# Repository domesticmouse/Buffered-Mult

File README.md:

# Buffered-Mult

A 3-channel active buffered mult (multiple) circuit designed for Eurorack modular synthesizers. View this in [KiCanvas](https://kicanvas.org/?repo=https%3A%2F%2Fgithub.com%2Fdomesticmouse%2FBuffered-Mult).

See [domesticmouse/BufferedMult-SKiDL](https://github.com/domesticmouse/BufferedMult-SKiDL) for an improved (and simplified) re-implementation.

## Purpose

In modular synthesis, a **multiple** is used to split a single signal (such as control voltage, gates/triggers, or audio) and route it to multiple destinations simultaneously.

While passive multiples simply wire jacks together in parallel, they cause **voltage droop** when splitting precise voltages like 1V/Octave pitch CV across multiple inputs due to impedance loading. This results in out-of-tune oscillators and pitch tracking errors.

This **buffered mult circuit** solves that problem by using active operational amplifiers configured as unity-gain buffers:

- **1:1 Voltage Precision:** Maintains accurate voltage levels (essential for 1V/Oct pitch CV) across all outputs without signal drop.
- **Impedance Isolation:** High input impedance presents virtually no load to the source signal, while low output impedance cleanly drives downstream module inputs.
- **Channel Isolation:** Prevents attached modules from loading or interfering with each other.

---

## Specifications

### Dimensions
- **Height:** 3U (Eurorack format)
- **Width:** 6HP
- **Faceplate:** Complete mechanical specifications and KiCad panel design are available in [`faceplate/README.md`](faceplate/README.md).

See Exploding Shed's [Eurorack Dimensions Guide](https://www.exploding-shed.com/synth-diy-guides/standards-of-eurorack/eurorack-dimensions/) for sizing a 6hp module.

### Inputs
- **3× 3.5 mm mono input jacks:**
  - Input 2 is normalled to Input 1.
  - Input 3 is normalled to Input 2.
- **Cascading Normalling Routing:**
  - **1 Input patched (Input 1):** Functions as a **1×9** mult (1 input split to 9 outputs).
  - **2 Inputs patched (Inputs 1 & 2):** Functions as **1×3** (Input 1) and **1×6** (Input 2) mults.
  - **3 Inputs patched (Inputs 1, 2 & 3):** Functions as **3 independent 1×3** mults.
- **100 kΩ pulldown resistors** (`R1`–`R3`) on inputs to prevent floating inputs when unpatched.
- **Input ESD & RF Filtering:** 1 kΩ series resistors (`R16`–`R18`) and 100 pF capacitors (`C9`–`C11`) provide high-frequency noise filtering and ESD protection.

### Outputs
- **9× 3.5 mm mono output jacks:** 3 dedicated buffered outputs for each of the 3 input channels.
- **1 kΩ Short-Circuit Protection:** Output series resistors (`R7`–`R15`) protect op-amps during cable insertion/patching shorts while maintaining stability under capacitive cable loads.
- **Bipolar LED Indication:** Opposing-polarity LED pairs (`D1`–`D6`) driven by dedicated active op-amp constant-current stages (`R4`–`R6`) indicate positive (+) and negative (-) voltage states without loading signal lines.

---

## Circuit & Physical Design

- **TL074 Quad Operational Amplifiers:** Configured as high-impedance unity-gain buffers (`U1`, `U2`, `U3`).
- **Active Visual Feedback:** 4th op-amp stage on each TL074 drives bipolar indicator LEDs in a constant-current feedback arrangement.
- **Power Connector:** Standard 2×5-pin IDC header (`J1`) for Eurorack ±12V power connection.
- **Power Filtering & Decoupling:** Bulk 10 µF electrolytic capacitors (`C7`, `C8`) on power entry rails plus 100 nF ceramic decoupling capacitors (`C1`–`C6`) per IC package.
- **Reverse Power Protection:** MBR0520 Schottky diodes (`D7`, `D8`) protect against reverse ribbon cable insertion.
- **Two-Sided Board Layout:** All SMT components on top layer (`F.Cu`); through-hole jacks and LEDs on bottom layer (`B.Cu`) for front panel mounting.

---

## Verification & Fabrication

- **KiCad Electrical Rules Check (ERC):** 0 Errors, 0 Warnings on main board schematic.
- **KiCad Design Rules Check (DRC):** 0 Track / Clearance Errors on main board and faceplate PCB.
- **JLCPCB Automated Assembly Ready:** Complete Gerber ZIP, SMT BOM (`BOM-Buffered-Mult.csv`), and Centroid CPL (`CPL-Buffered-Mult.csv`) generated in [`jlcpcb/production_files/`](jlcpcb/production_files/).
- **Faceplate Fabrication:** Complete KiCad project, panel Gerber files, and drill specs in [`faceplate/`](faceplate/).

## License

BufferedMult is open source and available under the [Apache License 2.0](LICENSE).

## Disclaimer

This is not an official Google product.

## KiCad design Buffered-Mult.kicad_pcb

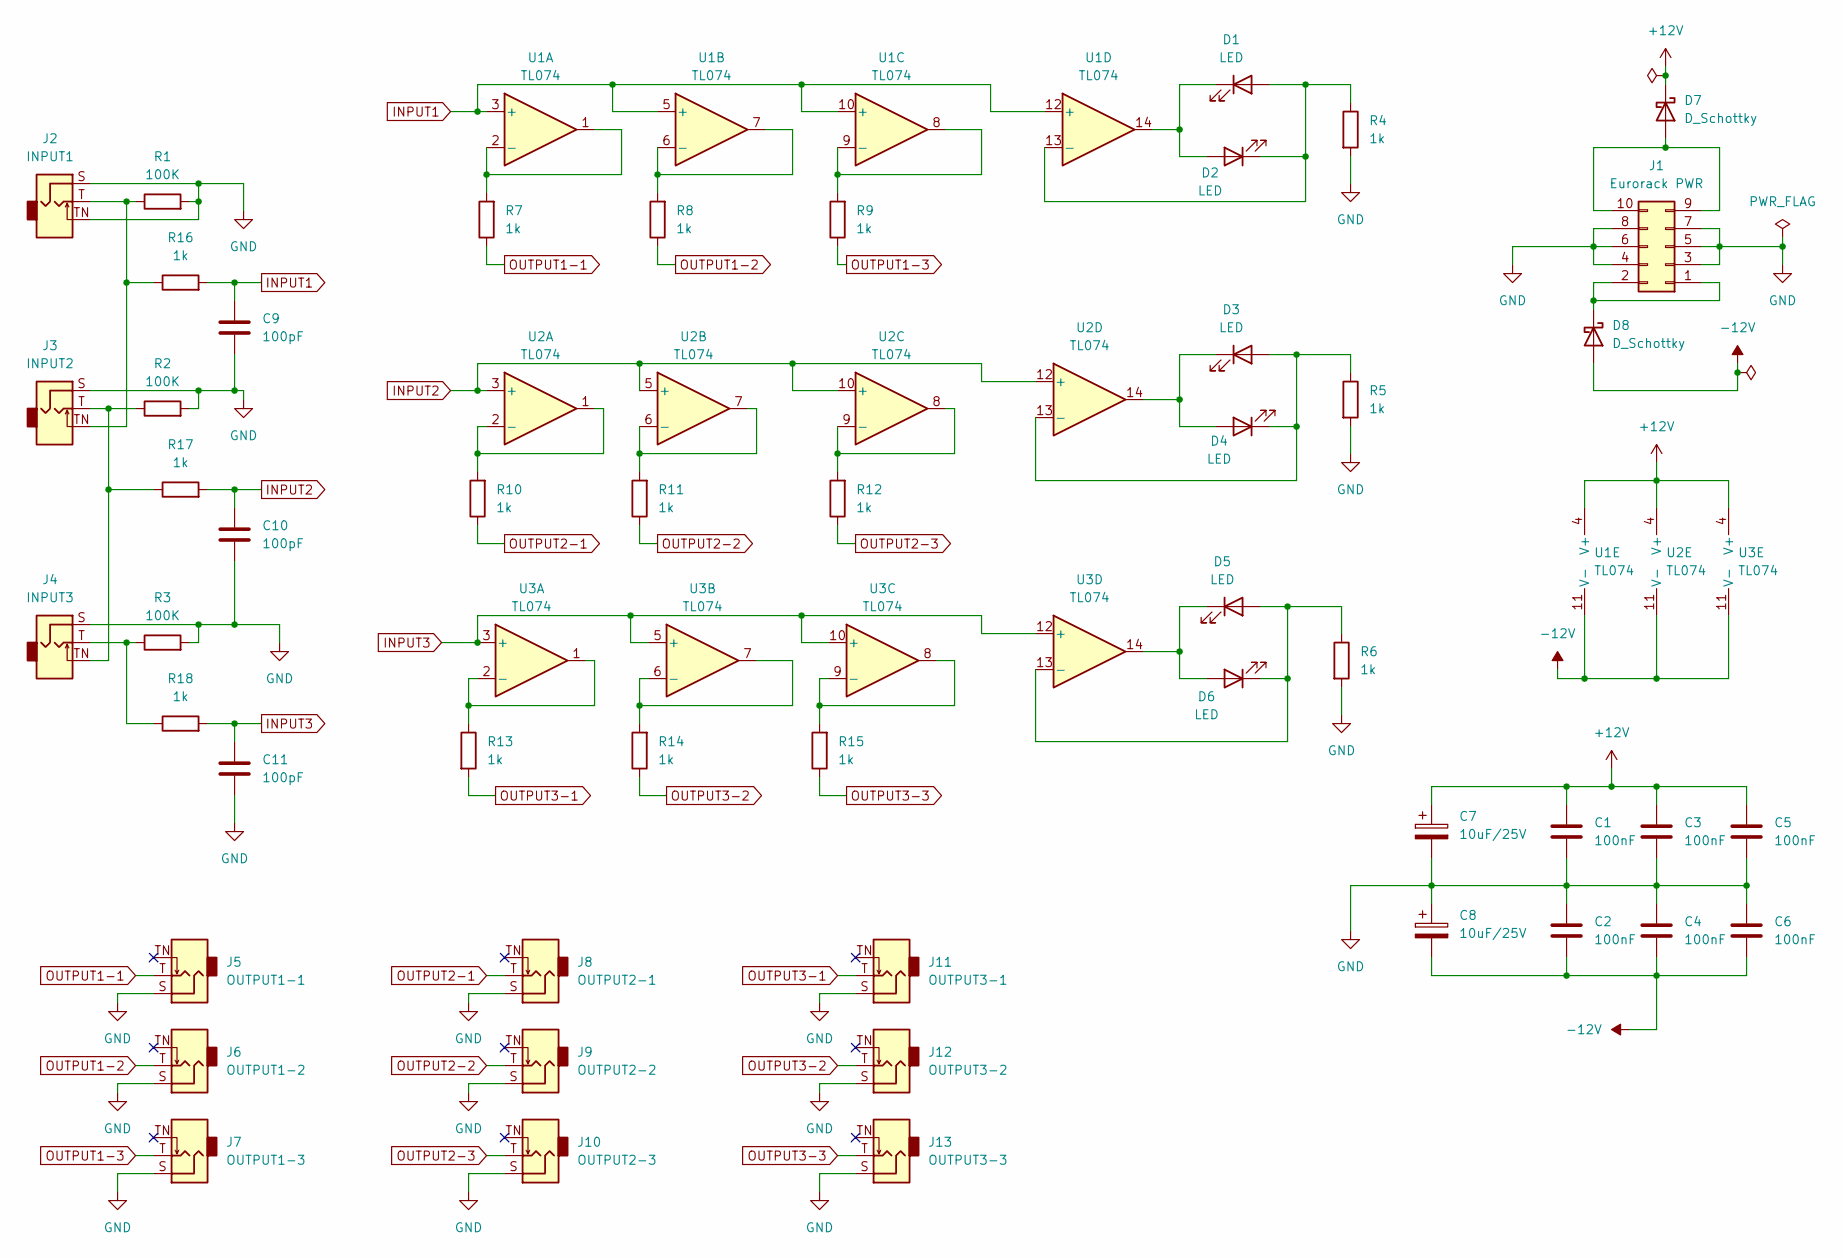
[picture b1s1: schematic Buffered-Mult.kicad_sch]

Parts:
C1, C2, C3, C4, C5, C6: 100nF; C_0603_1608Metric_Pad1.08x0.95mm_HandSolder; LCSC C14663
C7, C8: 10uF/25V; CP_Elec_5x5.4; LCSC C46550416
C9, C10, C11: 100pF; C_0603_1608Metric_Pad1.08x0.95mm_HandSolder; LCSC C14858
D1, D2, D3, D4, D5, D6: LED; LED_D3.0mm_FlatTop
D7, D8: D_Schottky; D_SMA_Handsoldering; LCSC C2480
J1: Eurorack PWR; IDC-Header_2x05_P2.54mm_Vertical
J2: INPUT1; Jack_3.5mm_QingPu_WQP-PJ398SM_Vertical_CircularHoles
J3: INPUT2; Jack_3.5mm_QingPu_WQP-PJ398SM_Vertical_CircularHoles
J4: INPUT3; Jack_3.5mm_QingPu_WQP-PJ398SM_Vertical_CircularHoles
J5: OUTPUT1-1; Jack_3.5mm_QingPu_WQP-PJ398SM_Vertical_CircularHoles
J6: OUTPUT1-2; Jack_3.5mm_QingPu_WQP-PJ398SM_Vertical_CircularHoles
J7: OUTPUT1-3; Jack_3.5mm_QingPu_WQP-PJ398SM_Vertical_CircularHoles
J8: OUTPUT2-1; Jack_3.5mm_QingPu_WQP-PJ398SM_Vertical_CircularHoles
J9: OUTPUT2-2; Jack_3.5mm_QingPu_WQP-PJ398SM_Vertical_CircularHoles
J10: OUTPUT2-3; Jack_3.5mm_QingPu_WQP-PJ398SM_Vertical_CircularHoles
J11: OUTPUT3-1; Jack_3.5mm_QingPu_WQP-PJ398SM_Vertical_CircularHoles
J12: OUTPUT3-2; Jack_3.5mm_QingPu_WQP-PJ398SM_Vertical_CircularHoles
J13: OUTPUT3-3; Jack_3.5mm_QingPu_WQP-PJ398SM_Vertical_CircularHoles
R1, R2, R3: 100K; R_0603_1608Metric_Pad0.98x0.95mm_HandSolder; LCSC C25803
R4, R5, R6, R7, R8, R9, R10, R11, R12, R13, R14, R15, R16, R17, R18: 1k; R_0603_1608Metric_Pad0.98x0.95mm_HandSolder; LCSC C21190
U1, U2, U3: TL074; SOIC-14_3.9x8.7mm_P1.27mm; LCSC C2878713

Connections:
+12V: C1.1, C3.1, C5.1, C7.1, D7.1 (K), U1.4 (V+), U2.4 (V+), U3.4 (V+)
-12V: C2.2, C4.2, C6.2, C8.2, D8.2 (A), U1.11 (V-), U2.11 (V-), U3.11 (V-)
GND: C1.2, C2.1, C3.2, C4.1, C5.2, C6.1, C7.2, C8.1, C9.2, C10.2, C11.2, J1.3, J1.4, J1.5, J1.6, J1.7, J1.8, J2.S, J2.TN, J3.S, J4.S, J5.S, J6.S, J7.S, J8.S, J9.S, J10.S, J11.S, J12.S, J13.S, R1.2, R2.2, R3.2, R4.2, R5.2, R6.2
INPUT1: C9.1, R16.2, U1.3 (+), U1.5 (+), U1.10 (+), U1.12 (+)
INPUT2: C10.1, R17.2, U2.3 (+), U2.5 (+), U2.10 (+), U2.12 (+)
INPUT3: C11.1, R18.2, U3.3 (+), U3.5 (+), U3.10 (+), U3.12 (+)
unnamed: D1.2 (A), D2.1 (K), R4.1, U1.13 (-)
unnamed: D1.1 (K), D2.2 (A), U1.14
unnamed: D3.2 (A), D4.1 (K), R5.1, U2.13 (-)
unnamed: D3.1 (K), D4.2 (A), U2.14
unnamed: D5.2 (A), D6.1 (K), R6.1, U3.13 (-)
unnamed: D5.1 (K), D6.2 (A), U3.14
unnamed: D7.2 (A), J1.9, J1.10
unnamed: D8.1 (K), J1.1, J1.2
unnamed: J2.T, J3.TN, R1.1, R16.1
unnamed: J3.T, J4.TN, R2.1, R17.1
unnamed: J4.T, R3.1, R18.1
unnamed: R7.2, U1.1, U1.2 (-)
unnamed: R8.2, U1.6 (-), U1.7
unnamed: R9.2, U1.8, U1.9 (-)
unnamed: R10.2, U2.1, U2.2 (-)
unnamed: R11.2, U2.6 (-), U2.7
unnamed: R12.2, U2.8, U2.9 (-)
unnamed: R13.1, U3.1, U3.2 (-)
unnamed: R14.2, U3.6 (-), U3.7
unnamed: R15.2, U3.8, U3.9 (-)
OUTPUT1-1: J5.T, R7.1
OUTPUT1-2: J6.T, R8.1
OUTPUT1-3: J7.T, R9.1
OUTPUT2-1: J8.T, R10.1
OUTPUT2-2: J9.T, R11.1
OUTPUT2-3: J10.T, R12.1
OUTPUT3-1: J11.T, R13.2
OUTPUT3-2: J12.T, R14.1
OUTPUT3-3: J13.T, R15.1

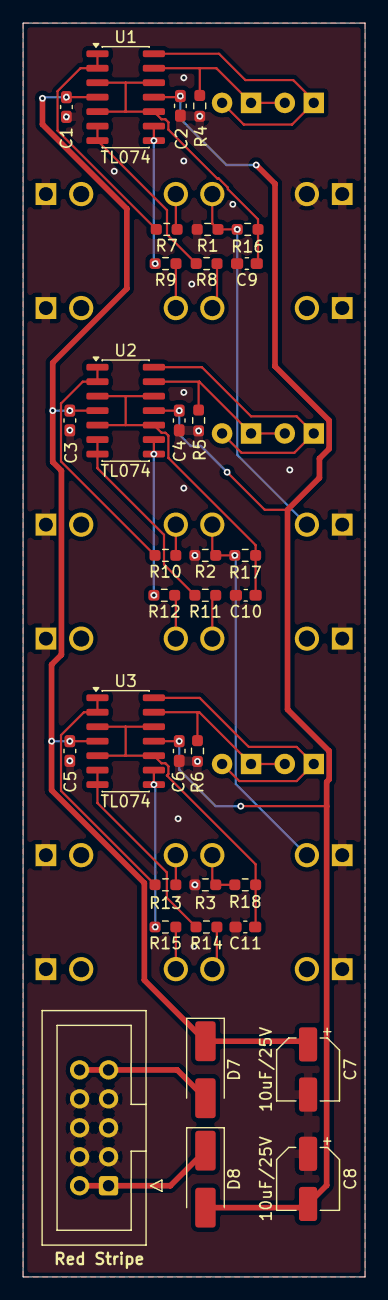
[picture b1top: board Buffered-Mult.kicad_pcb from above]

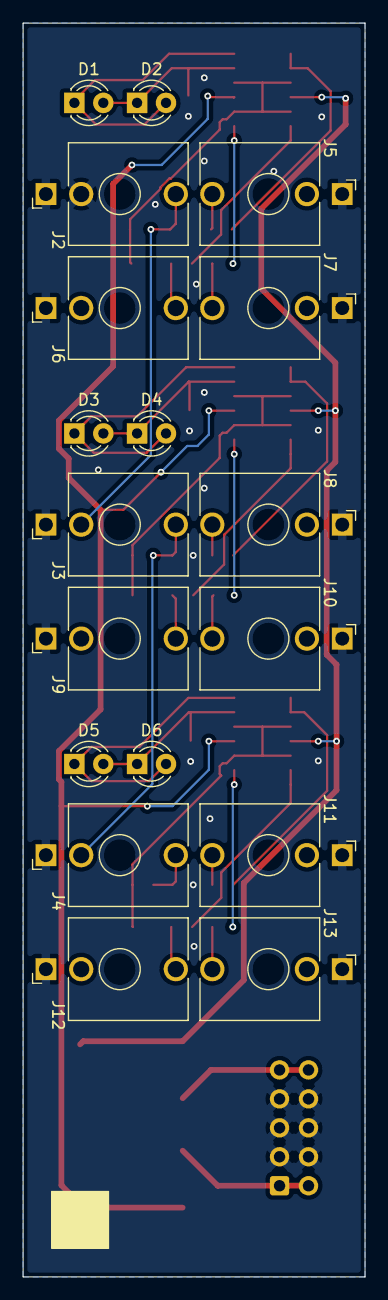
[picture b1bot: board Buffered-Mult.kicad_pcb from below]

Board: 2 copper layers, 30.0 x 110.0 mm, 53 parts (18 on the bottom side), 35 nets.

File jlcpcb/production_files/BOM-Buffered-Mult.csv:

Comment,Designator,Footprint,LCSC,Quantity
100K,"R1,R2,R3",R_0603_1608Metric_Pad0.98x0.95mm_HandSolder,C25803,3
100nF,"C1,C2,C3,C4,C5,C6",C_0603_1608Metric_Pad1.08x0.95mm_HandSolder,C14663,6
100pF,"C10,C11,C9",C_0603_1608Metric_Pad1.08x0.95mm_HandSolder,C14858,3
10uF/25V,"C7,C8",CP_Elec_5x5.4,C46550416,2
1k,"R10,R11,R12,R13,R14,R15,R16,R17,R18,R4,R5,R6,R7,R8,R9",R_0603_1608Metric_Pad0.98x0.95mm_HandSolder,C21190,15
D_Schottky,"D7,D8",D_SMA_Handsoldering,C2480,2
TL074,"U1,U2,U3",SOIC-14_3.9x8.7mm_P1.27mm,C2878713,3
OUTPUT3-3,J13,Jack_3.5mm_QingPu_WQP-PJ398SM_Vertical_CircularHoles,,1
OUTPUT3-2,J12,Jack_3.5mm_QingPu_WQP-PJ398SM_Vertical_CircularHoles,,1
OUTPUT3-1,J11,Jack_3.5mm_QingPu_WQP-PJ398SM_Vertical_CircularHoles,,1
OUTPUT2-3,J10,Jack_3.5mm_QingPu_WQP-PJ398SM_Vertical_CircularHoles,,1
OUTPUT2-2,J9,Jack_3.5mm_QingPu_WQP-PJ398SM_Vertical_CircularHoles,,1
OUTPUT2-1,J8,Jack_3.5mm_QingPu_WQP-PJ398SM_Vertical_CircularHoles,,1
OUTPUT1-3,J7,Jack_3.5mm_QingPu_WQP-PJ398SM_Vertical_CircularHoles,,1
OUTPUT1-2,J6,Jack_3.5mm_QingPu_WQP-PJ398SM_Vertical_CircularHoles,,1
OUTPUT1-1,J5,Jack_3.5mm_QingPu_WQP-PJ398SM_Vertical_CircularHoles,,1
INPUT3,J4,Jack_3.5mm_QingPu_WQP-PJ398SM_Vertical_CircularHoles,,1
INPUT2,J3,Jack_3.5mm_QingPu_WQP-PJ398SM_Vertical_CircularHoles,,1
INPUT1,J2,Jack_3.5mm_QingPu_WQP-PJ398SM_Vertical_CircularHoles,,1
Eurorack PWR,J1,IDC-Header_2x05_P2.54mm_Vertical,,1
LED,D6,LED_D3.0mm_FlatTop,,1
LED,D5,LED_D3.0mm_FlatTop,,1
LED,D4,LED_D3.0mm_FlatTop,,1
LED,D3,LED_D3.0mm_FlatTop,,1
LED,D2,LED_D3.0mm_FlatTop,,1
LED,D1,LED_D3.0mm_FlatTop,,1
